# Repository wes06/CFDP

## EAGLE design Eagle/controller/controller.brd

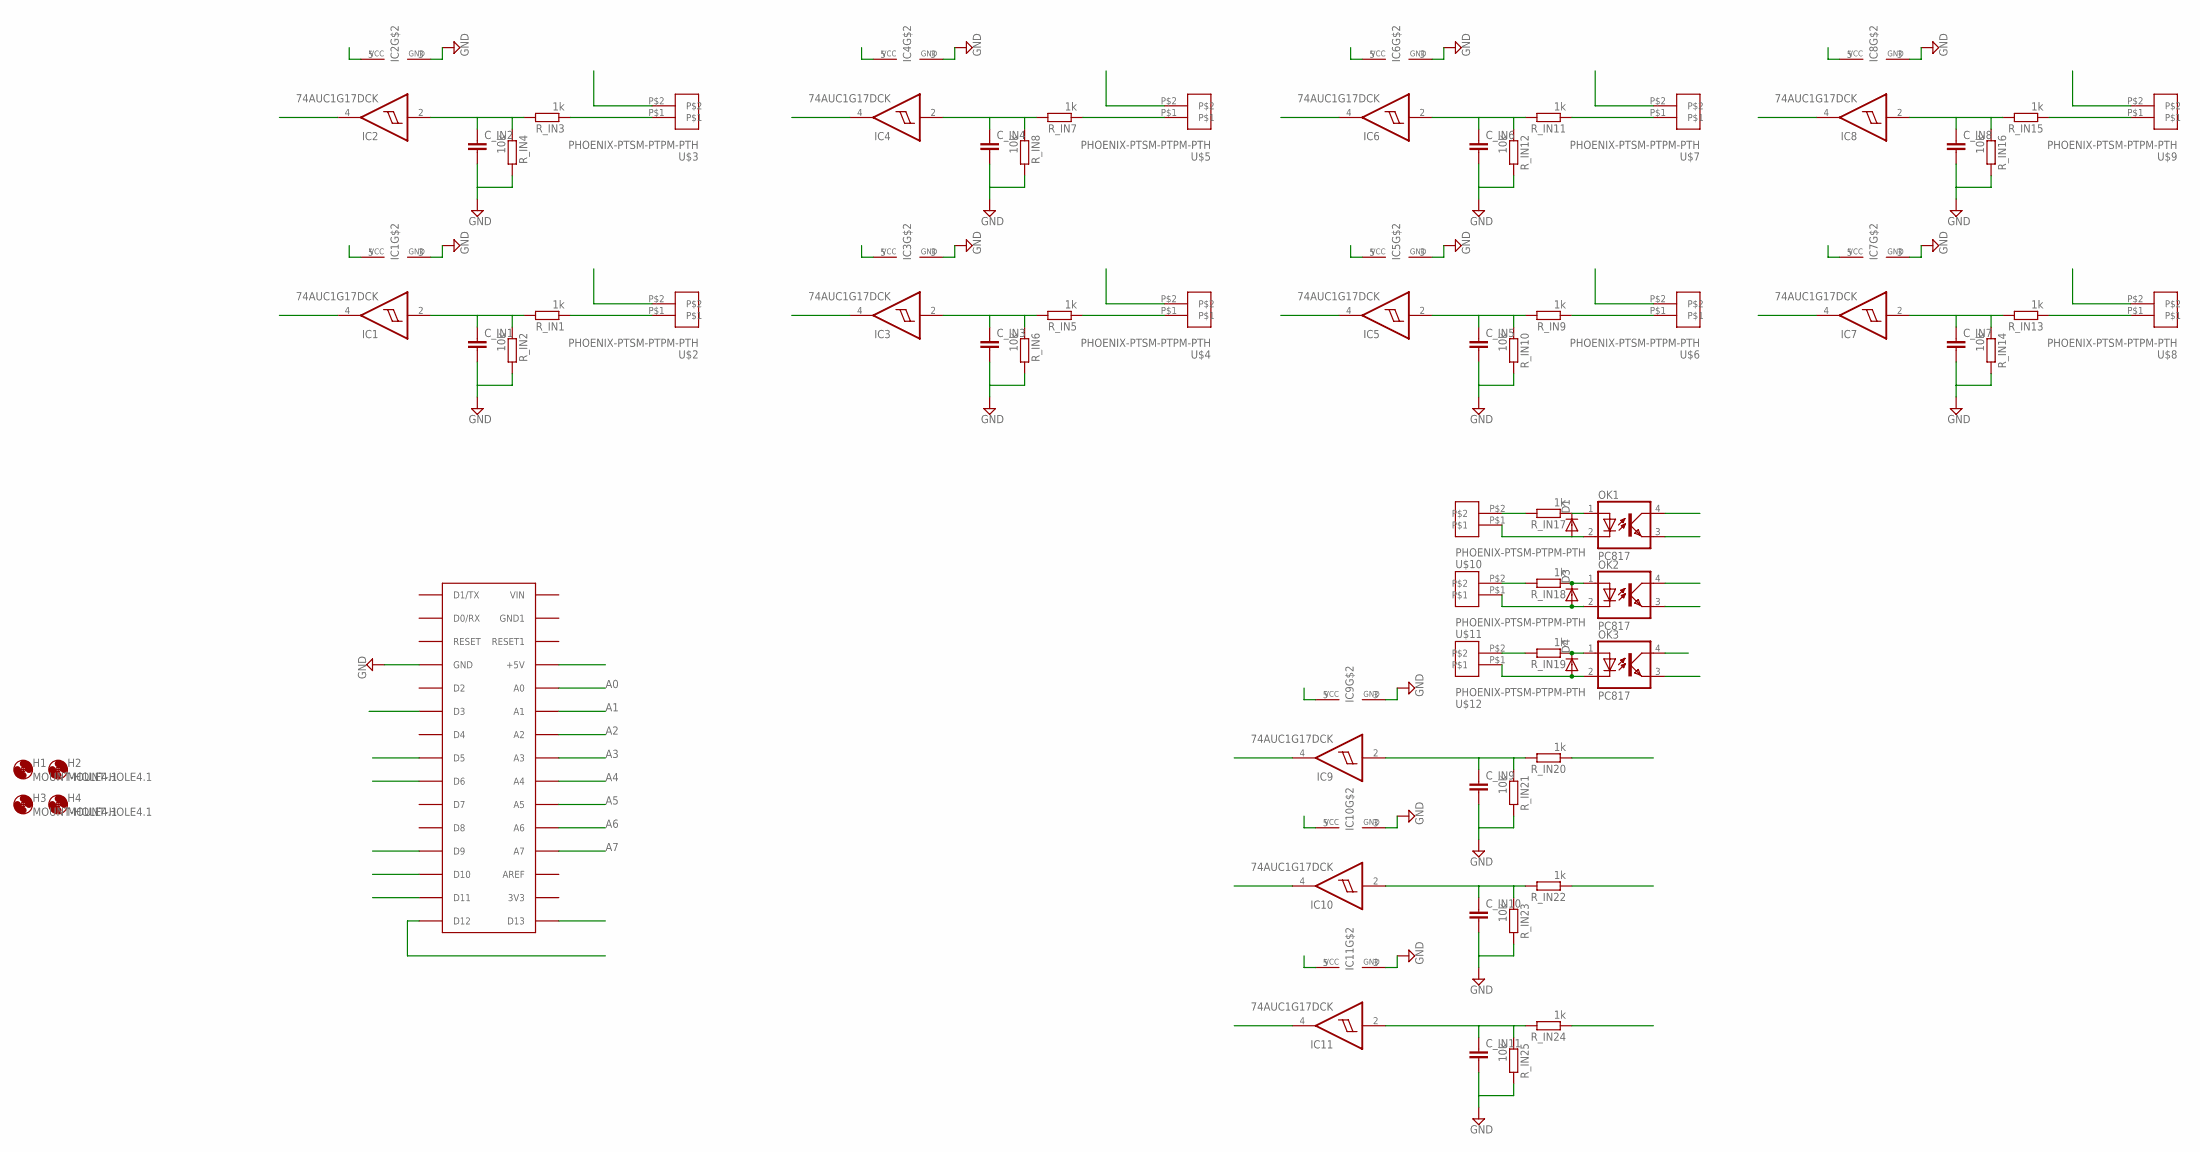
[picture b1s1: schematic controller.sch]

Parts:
C_IN1, C_IN2, C_IN3, C_IN4, C_IN5, C_IN6, C_IN7, C_IN8, C_IN9, C_IN10, C_IN11: C-EUC0805; C0805
D1, D3, D4: DIODE-DO-214AC; DO-214AC
H1, H2, H3, H4: MOUNT-HOLE4.1; 4,1
IC1, IC2, IC3, IC4, IC5, IC6, IC7, IC8, IC9, IC10, IC11: 74AUC1G17DCK; SC70-5
OK1, OK2: PC817; DIL04
OK3: PC817; DIL04; MPN PC817X4J000F
R_IN1, R_IN3, R_IN5, R_IN7, R_IN9, R_IN11, R_IN13, R_IN15, R_IN20, R_IN22, R_IN24: 1k; M0805
R_IN2, R_IN4, R_IN6, R_IN8, R_IN10, R_IN12, R_IN14, R_IN16, R_IN21, R_IN23, R_IN25: 10k; M0805
R_IN17, R_IN18, R_IN19: 1k; M1206
U$1: ARDUINONANO; PDIP-32
U$2, U$3, U$4, U$5, U$6, U$7, U$8, U$9, U$10, U$11, U$12: PHOENIX-PTSM-PTPM-PTH; PTSM-PTH-2.5MM-2

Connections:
+5V: IC1.5 (VCC), IC2.5 (VCC), IC3.5 (VCC), IC4.5 (VCC), IC5.5 (VCC), IC6.5 (VCC), IC7.5 (VCC), IC8.5 (VCC), OK1.4 (COL), OK2.4 (COL), OK3.4 (COL), U$1.+5V, U$2.P$2, U$3.P$2, U$4.P$2, U$5.P$2, U$6.P$2, U$7.P$2, U$8.P$2, U$9.P$2
+5V1: IC9.5 (VCC)
+5V2: IC10.5 (VCC)
+5V3: IC11.5 (VCC)
A0: IC1.4 (O), U$1.A0
A1: IC2.4 (O), U$1.A1
A2: IC3.4 (O), U$1.A2
A3: IC4.4 (O), U$1.A3
A4: IC5.4 (O), U$1.A4
A5: IC6.4 (O), U$1.A5
A6: IC7.4 (O), U$1.A6
A7: IC8.4 (O), U$1.A7
A8: R_IN3.1, U$3.P$1
A9: R_IN5.1, U$4.P$1
A10: R_IN7.1, U$5.P$1
A11: R_IN9.1, U$6.P$1
A12: R_IN11.1, U$7.P$1
A13: R_IN13.1, U$8.P$1
A14: R_IN15.1, U$9.P$1
A15: IC9.4 (O)
A16: IC10.4 (O)
A17: IC11.4 (O)
GND: C_IN1.2, C_IN2.2, C_IN3.2, C_IN4.2, C_IN5.2, C_IN6.2, C_IN7.2, C_IN8.2, C_IN9.2, C_IN10.2, C_IN11.2, IC1.3 (GND), IC2.3 (GND), IC3.3 (GND), IC4.3 (GND), IC5.3 (GND), IC6.3 (GND), IC7.3 (GND), IC8.3 (GND), IC9.3 (GND), IC10.3 (GND), IC11.3 (GND), R_IN2.2, R_IN4.2, R_IN6.2, R_IN8.2, R_IN10.2, R_IN12.2, R_IN14.2, R_IN16.2, R_IN21.2, R_IN23.2, R_IN25.2, U$1.GND
unnamed: C_IN9.1, IC9.2 (I), R_IN20.2, R_IN21.1
unnamed: C_IN2.1, IC2.2 (I), R_IN3.2, R_IN4.1
unnamed: D3.C, OK2.1 (A), R_IN18.1
unnamed: C_IN3.1, IC3.2 (I), R_IN5.2, R_IN6.1
unnamed: D4.C, OK3.1 (A), R_IN19.1
unnamed: C_IN4.1, IC4.2 (I), R_IN7.2, R_IN8.1
unnamed: D1.C, OK1.1 (A), R_IN17.1
unnamed: C_IN5.1, IC5.2 (I), R_IN9.2, R_IN10.1
unnamed: D3.A, OK2.2 (C), U$11.P$1
unnamed: C_IN6.1, IC6.2 (I), R_IN11.2, R_IN12.1
unnamed: D4.A, OK3.2 (C), U$12.P$1
unnamed: C_IN7.1, IC7.2 (I), R_IN13.2, R_IN14.1
unnamed: R_IN17.2, U$10.P$2
unnamed: C_IN8.1, IC8.2 (I), R_IN15.2, R_IN16.1
unnamed: C_IN1.1, IC1.2 (I), R_IN1.2, R_IN2.1
unnamed: R_IN18.2, U$11.P$2
unnamed: R_IN19.2, U$12.P$2
unnamed: D1.A, OK1.2 (C), U$10.P$1
unnamed: C_IN10.1, IC10.2 (I), R_IN22.2, R_IN23.1
unnamed: C_IN11.1, IC11.2 (I), R_IN24.2, R_IN25.1
unnamed: OK1.3 (EMIT), R_IN20.1
unnamed: OK2.3 (EMIT), R_IN22.1
unnamed: OK3.3 (EMIT), R_IN24.1
unnamed: R_IN1.1, U$2.P$1
PWM1: U$1.D3
PWM2: U$1.D5
PWM3: U$1.D6
PWM4: U$1.D9
PWM5: U$1.D10
PWM6: U$1.D11

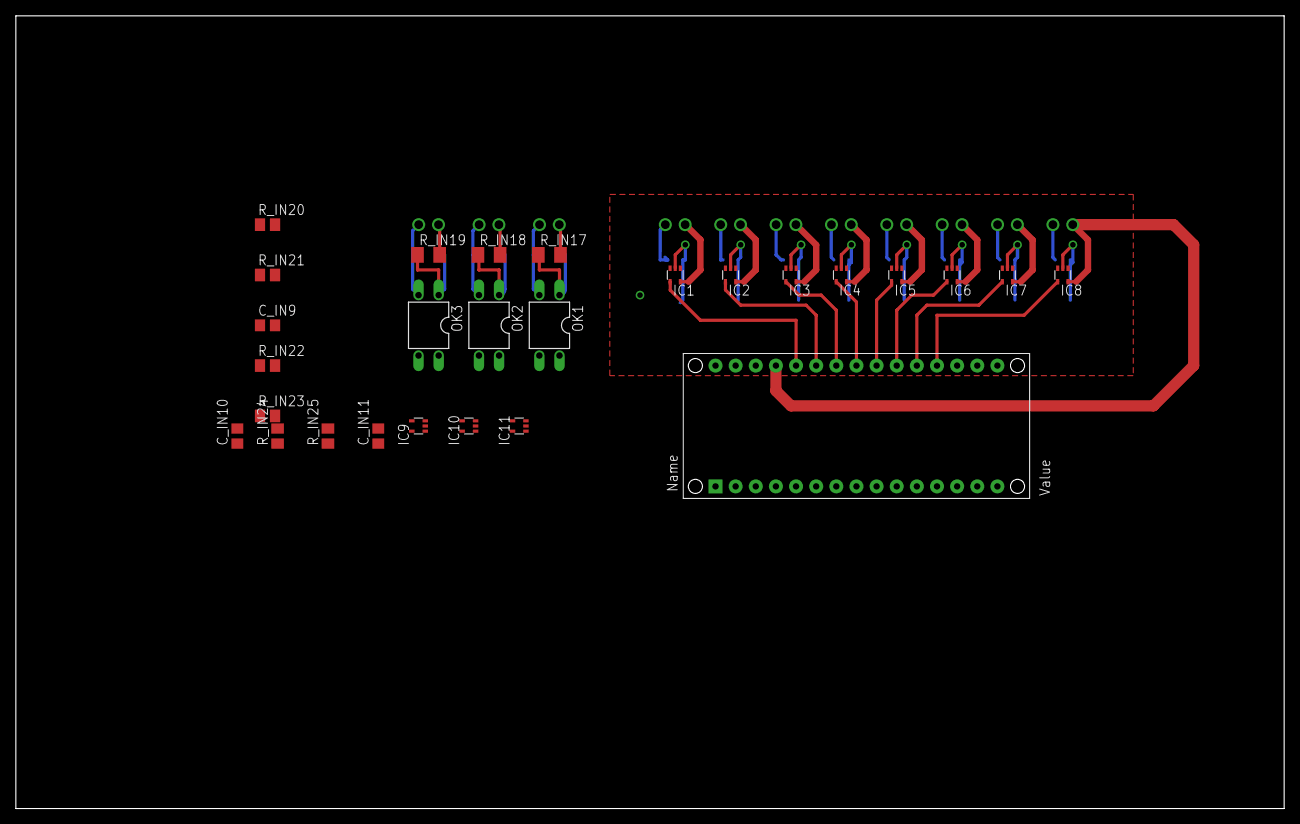
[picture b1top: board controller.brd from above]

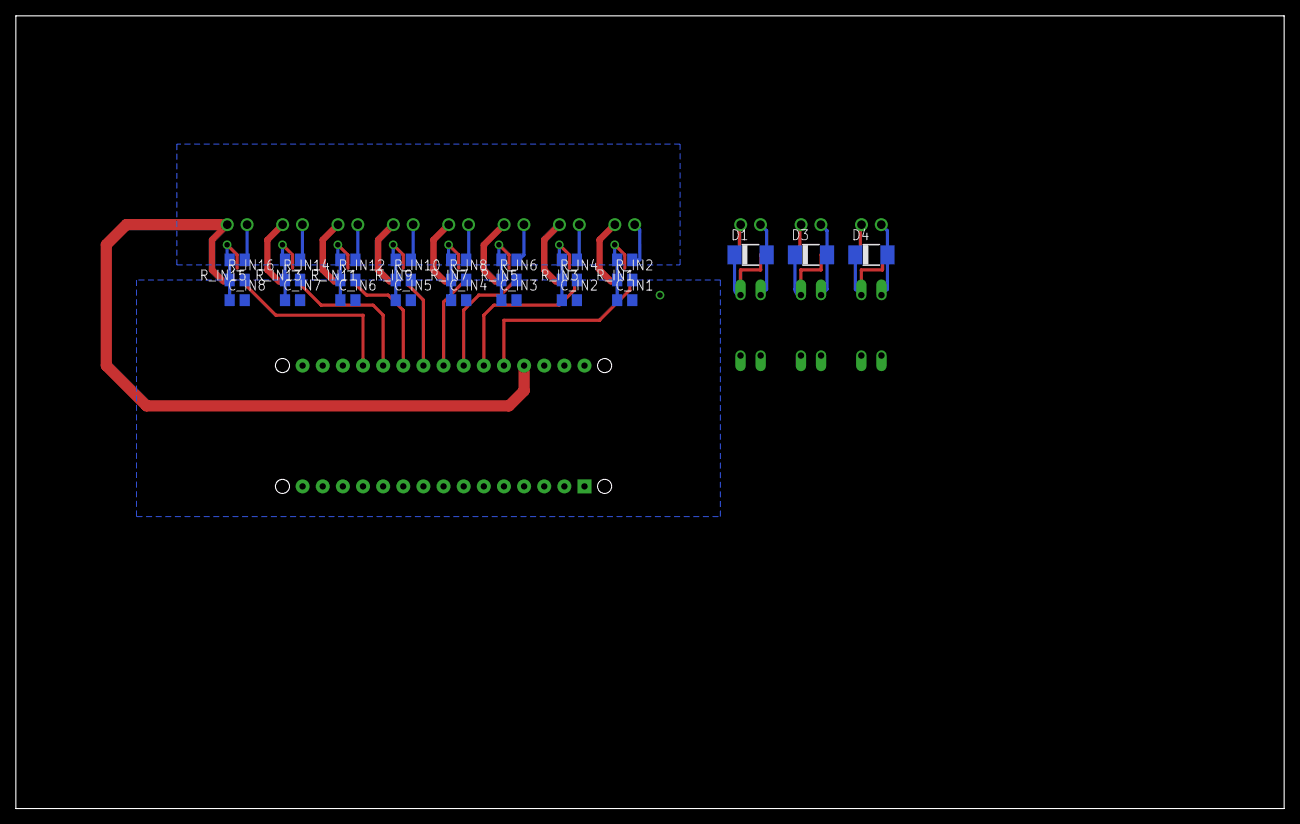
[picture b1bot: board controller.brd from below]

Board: 2 copper layers, 160.0 x 100.0 mm, 69 parts (27 on the bottom side), 41 nets.

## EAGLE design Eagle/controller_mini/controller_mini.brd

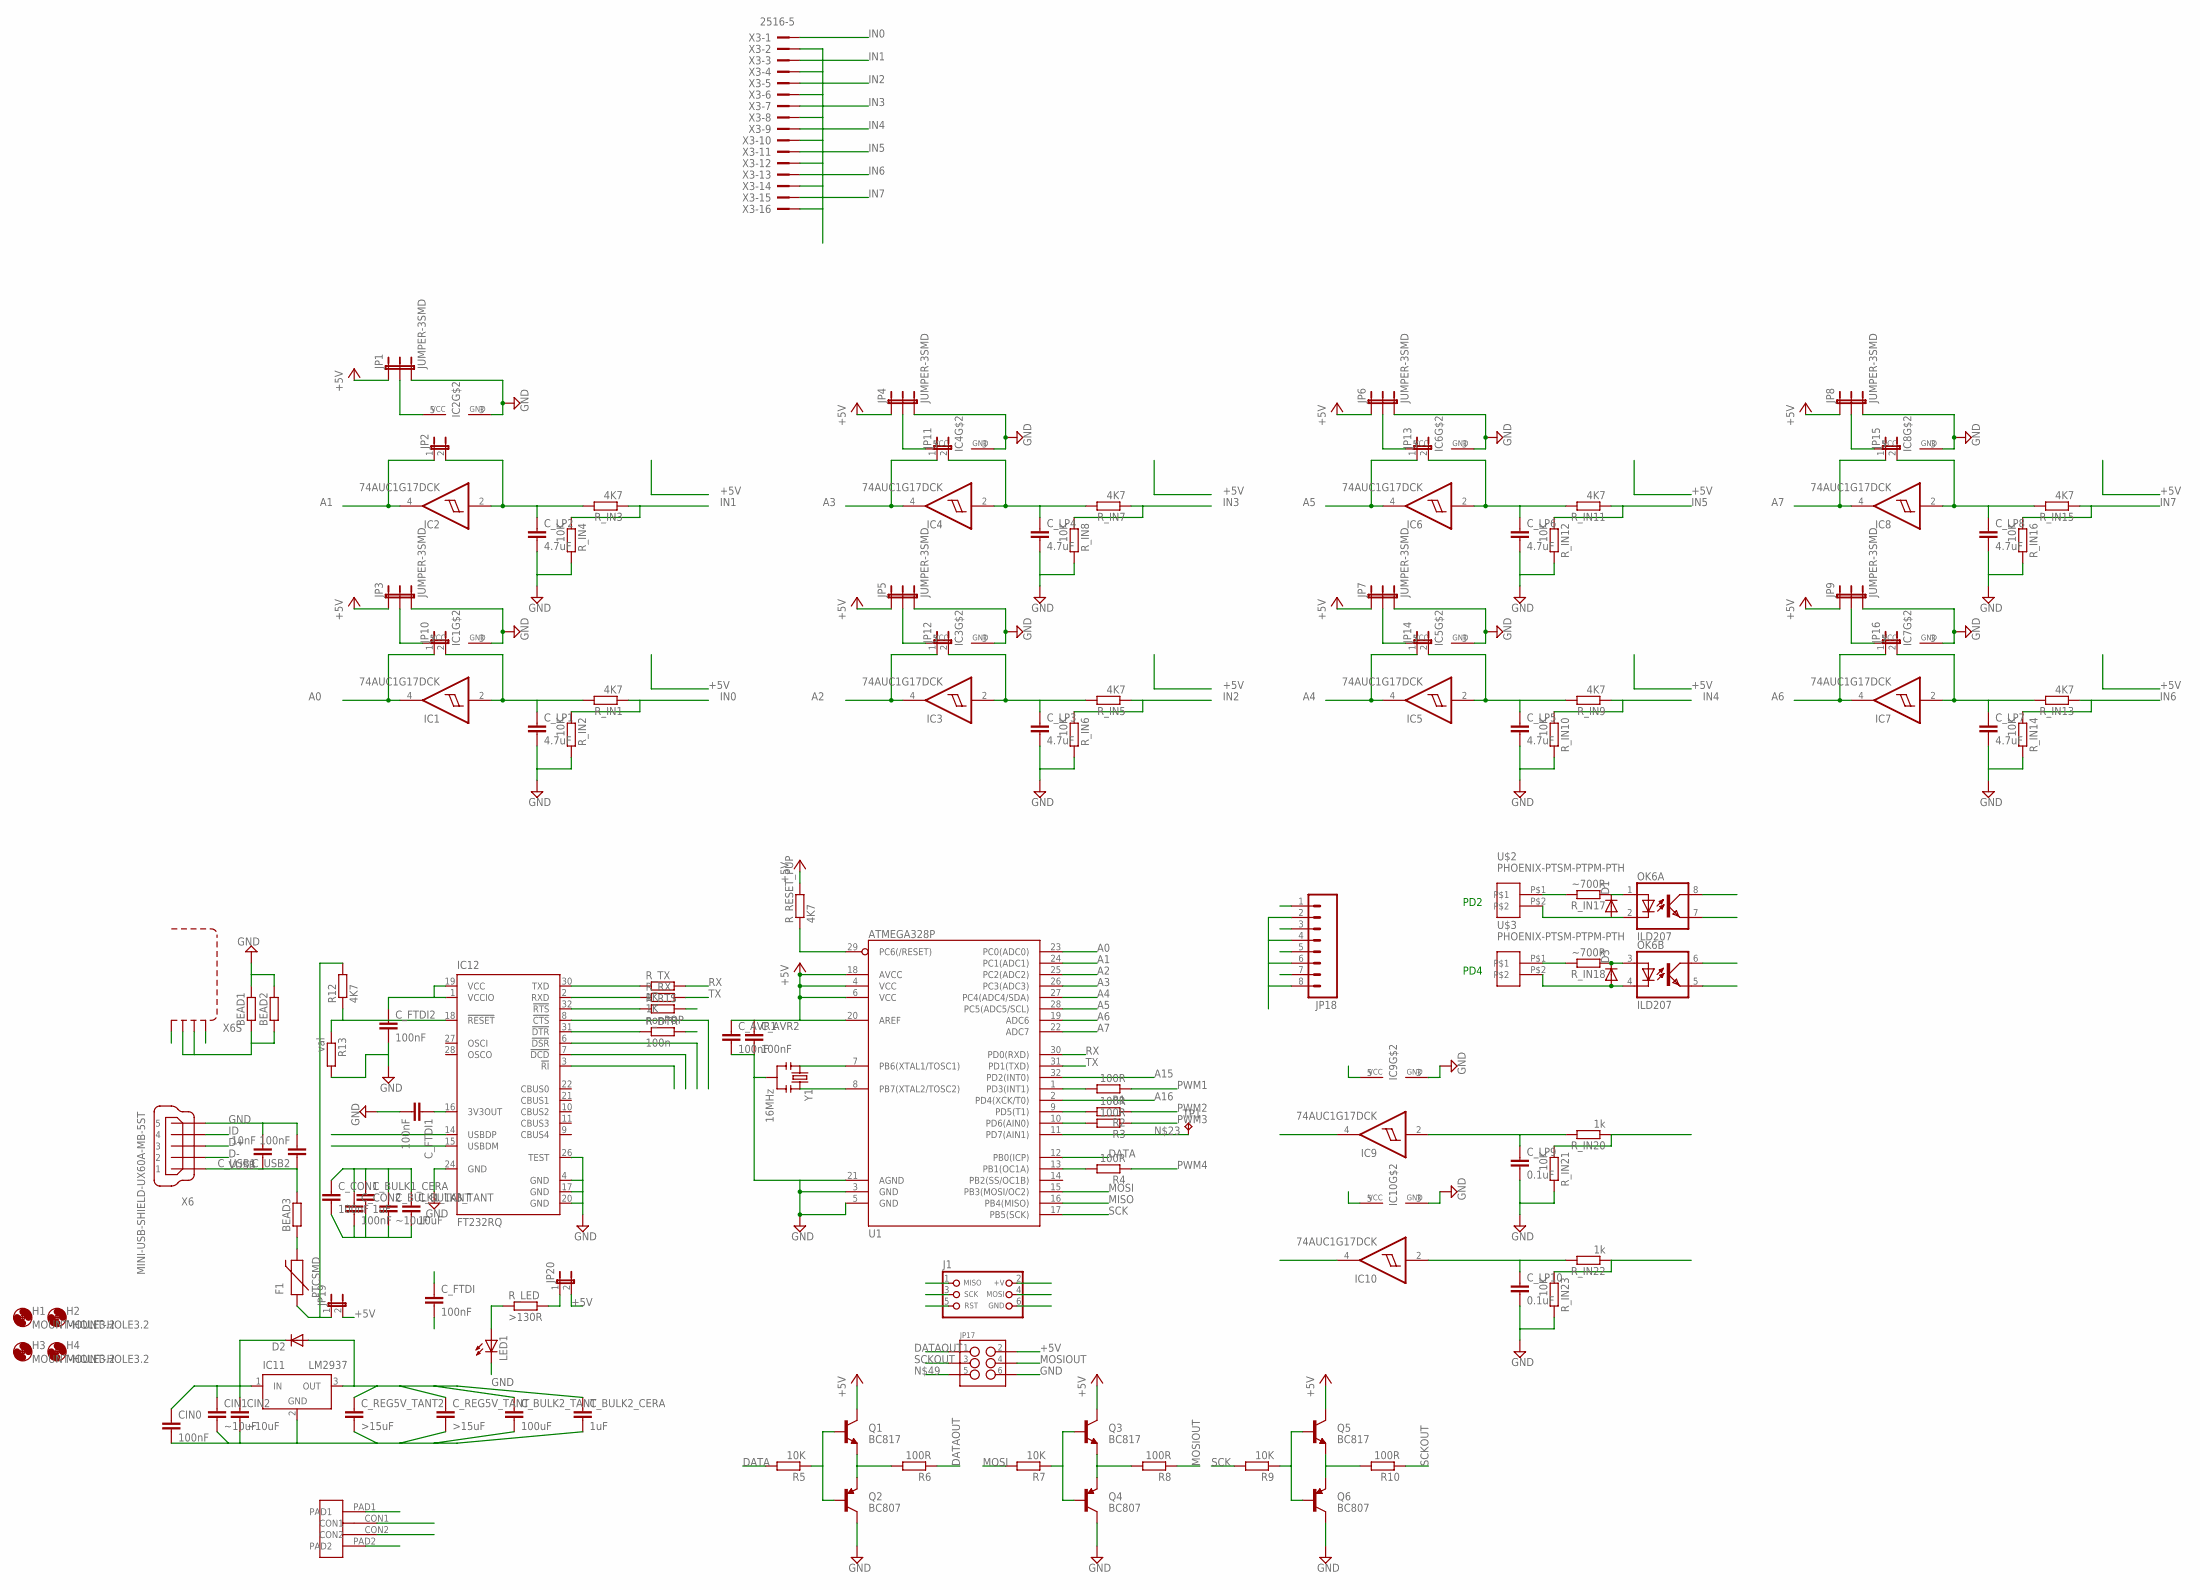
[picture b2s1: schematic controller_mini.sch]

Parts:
BEAD1, BEAD2, BEAD3: R-EU_R0805; R0805
CIN0: 100nF; C0805
CIN1, CIN2: ~10uF; C1210
C_AVR1, C_AVR2: 100nF; C0805
C_BULK1_CERA, C_BULK2_CERA: 1uF; C0805K
C_BULK1_TANT: ~10uF; C1210
C_BULK2_TANT: 100uF; C1210
C_BULK3_TANT: 10uF; C1210
C_CON1, C_CON2: 100nF; C0805
C_FTDI, C_FTDI1, C_FTDI2: 100nF; C0805
C_LP1, C_LP2, C_LP3, C_LP4, C_LP5, C_LP6, C_LP7, C_LP8: 4.7uF; C0805
C_LP9, C_LP10: 0.1uF; C0805
C_REG5V_TANT, C_REG5V_TANT2: >15uF; C1210
C_USB1: 10nF; C0805
C_USB2: 100nF; C0805
D1, D3: DIODE-MICROMELF-W; MICROMELF-W
D2: DIODESMA; SMA-DIODE
F1: PTCSMD; PTC-1206
H1, H2, H3, H4: MOUNT-HOLE3.2; 3,2
IC1, IC2, IC3, IC4, IC5, IC6, IC7, IC8, IC9, IC10: 74AUC1G17DCK; SC70-5
IC11: LM2937; SOT223
IC12: FT232RQ; QFN32
J1: CON_HEADER_PRG_AVR_ICSP; HEADER_PRG_2X03
JP1, JP3, JP4, JP5, JP6, JP7, JP8, JP9: JUMPER-3SMD; SJ_3
JP2, JP10, JP11, JP12, JP13, JP14, JP15, JP16: JUMPER-2SMD-NO; SJ_2S-NO
JP17: M03X2NO_SILK; 2X3-NS
JP18: M08LOCK; 1X08_LOCK
JP19, JP20: JUMPER-2SMD-NC; SJ_2S
LED1: LEDCHIP-LED0805; CHIP-LED0805
OK6: ILD207; SOIC08
Q1, Q3, Q5: BC817; SOT23-3
Q2, Q4, Q6: BC807; SOT23-3
R1, R2, R3, R6, R8, R10: 100R; M0805
R4: 100R; R0805W
R5, R7, R9: 10K; M0805
R12: 4K7; R0805
R13: val; R0805
R_DTR: 100n; M0805
R_IN1, R_IN3, R_IN5, R_IN7, R_IN9, R_IN11, R_IN13, R_IN15: 4K7; M0805
R_IN2, R_IN4, R_IN6, R_IN8, R_IN10, R_IN12, R_IN14, R_IN16, R_IN21, R_IN23: 10K; M0805
R_IN17, R_IN18: ~700R; M1206
R_IN20, R_IN22: 1k; M0805
R_LED: >130R; M0805
R_RESET_PUP: 4K7; M0805
R_RTS: nonPOP; M0805
R_RX: 1K; M0805
R_TX: 1K; M0805
TP1: TPTP10R; TP10R
U1: ATMEGA328P; TQFP32-08
U$1: PHOENIX-PTSM-PTPM; PTSM-SMD-2.5MM-2
U$2, U$3: PHOENIX-PTSM-PTPM-PTH; PTSM-PTH-2.5MM-2
X3: 2516-5; PAK100/2500-5-16
X6: MINI-USB-SHIELD-UX60A-MB-5ST; UX60A-MB-5ST
Y1: 16MHz; RESONATOR-SMD

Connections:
+5V: C_AVR1.1, C_AVR2.1, C_BULK1_CERA.1, C_BULK1_TANT.1, C_BULK2_CERA.1, C_BULK2_TANT.1, C_BULK3_TANT.1, C_CON1.1, C_CON2.1, C_FTDI.1, C_FTDI2.1, C_REG5V_TANT.1, C_REG5V_TANT2.1, D2.A, IC9.5 (VCC), IC10.5 (VCC), IC11.3 (OUT), IC12.1 (VCCIO), IC12.19 (VCC), J1.2 (+V), JP1.1, JP3.1, JP4.1, JP5.1, JP6.1, JP7.1, JP8.1, JP9.1, JP17.2, JP19.2, JP20.2, OK6.6 (COL), OK6.8 (COL), Q1.3 (C), Q3.3 (C), Q5.3 (C), R_RESET_PUP.2, U1.4 (VCC), U1.6 (VCC), U1.18 (AVCC), U1.20 (AREF), X3.2, X3.4, X3.6, X3.8, X3.10, X3.12, X3.14, X3.16
A0: IC1.4 (O), JP10.1, U1.23 (PC0(ADC0))
A1: IC2.4 (O), JP2.1, U1.24 (PC1(ADC1))
A2: IC3.4 (O), JP12.1, U1.25 (PC2(ADC2))
A3: IC4.4 (O), JP11.1, U1.26 (PC3(ADC3))
A4: IC5.4 (O), JP14.1, U1.27 (PC4(ADC4/SDA))
A5: IC6.4 (O), JP13.1, U1.28 (PC5(ADC5/SCL))
A6: IC7.4 (O), JP16.1, U1.19 (ADC6)
A7: IC8.4 (O), JP15.1, U1.22 (ADC7)
A15: IC9.4 (O), U1.32 (PD2(INT0))
A16: IC10.4 (O), U1.2 (PD4(XCK/T0))
D+: IC12.14 (USBDP), X6.3
D-: IC12.15 (USBDM), X6.2
DATA: R5.2, U1.12 (PB0(ICP))
DATAOUT: JP17.1, R6.1
EROUTE: C_LP8.1, IC8.2 (I), JP15.2, R_IN15.2
GND: BEAD1.2, BEAD2.2, CIN0.2, CIN1.2, CIN2.2, C_AVR1.2, C_AVR2.2, C_BULK1_CERA.2, C_BULK1_TANT.2, C_BULK2_CERA.2, C_BULK2_TANT.2, C_BULK3_TANT.2, C_CON1.2, C_CON2.2, C_FTDI.2, C_FTDI1.2, C_FTDI2.2, C_LP1.2, C_LP2.2, C_LP3.2, C_LP4.2, C_LP5.2, C_LP6.2, C_LP7.2, C_LP8.2, C_LP9.2, C_LP10.2, C_REG5V_TANT.2, C_REG5V_TANT2.2, C_USB1.2, C_USB2.2, IC1.3 (GND), IC2.3 (GND), IC3.3 (GND), IC4.3 (GND), IC5.3 (GND), IC6.3 (GND), IC7.3 (GND), IC8.3 (GND), IC9.3 (GND), IC10.3 (GND), IC11.2 (GND), IC11.4 (GND), IC12.4 (GND), IC12.17 (GND), IC12.20 (GND), IC12.24 (GND), IC12.26 (TEST), J1.6 (GND), JP1.3, JP3.3, JP4.3, JP5.3, JP6.3, JP7.3, JP8.3, JP9.3, JP17.6, JP18.2, JP18.4, JP18.6, JP18.8, LED1.C, Q2.3 (C), Q4.3 (C), Q6.3 (C), R13.2, R_IN2.2, R_IN4.2, R_IN6.2, R_IN8.2, R_IN10.2, R_IN12.2, R_IN14.2, R_IN16.2, R_IN21.2, R_IN23.2, U1.3 (GND), U1.5 (GND), U1.21 (AGND), U$1.CON2, U$1.PAD1, U$1.PAD2, X6.5, Y1.2
ID: X6.4
IN0: R_IN1.1, R_IN2.1, X3.1
IN1: R_IN3.1, R_IN4.1, X3.3
IN2: R_IN5.1, R_IN6.1, X3.5
IN3: R_IN7.1, R_IN8.1, X3.7
IN4: R_IN9.1, R_IN10.1, X3.9
IN5: R_IN11.1, R_IN12.1, X3.11
IN6: R_IN13.1, R_IN14.1, X3.13
IN7: R_IN15.1, R_IN16.1, X3.15
INFOMOVE: D3.A, OK6.4 (C), U$3.P$2
MISO: J1.1 (MISO), U1.16 (PB4(MISO))
MOSI: J1.4 (MOSI), R7.2, U1.15 (PB3(MOSI/OC2))
MOSIOUT: JP17.4, R8.1
unnamed: C_LP9.1, IC9.2 (I), R_IN20.2
unnamed: C_LP2.1, IC2.2 (I), JP2.2, R_IN3.2
unnamed: D3.C, OK6.3 (A), R_IN18.1
unnamed: C_LP3.1, IC3.2 (I), JP12.2, R_IN5.2
unnamed: U1.7 (PB6(XTAL1/TOSC1)), Y1.1
unnamed: C_LP4.1, IC4.2 (I), JP11.2, R_IN7.2
unnamed: D1.C, OK6.1 (A), R_IN17.1
unnamed: C_LP5.1, IC5.2 (I), JP14.2, R_IN9.2
unnamed: BEAD3.1, F1.2
unnamed: C_LP6.1, IC6.2 (I), JP13.2, R_IN11.2
unnamed: U1.8 (PB7(XTAL2/TOSC2)), Y1.3
unnamed: C_LP7.1, IC7.2 (I), JP16.2, R_IN13.2
unnamed: R_IN17.2, U$2.P$1
unnamed: JP20.1, R_LED.2
unnamed: C_LP1.1, IC1.2 (I), JP10.2, R_IN1.2
unnamed: R_IN18.2, U$3.P$1
unnamed: Q1.2 (E), Q2.2 (E), R6.2
unnamed: D1.A, OK6.2 (C), U$2.P$2
unnamed: C_LP10.1, IC10.2 (I), R_IN22.2
unnamed: Q1.1 (B), Q2.1 (B), R5.1
unnamed: OK6.7 (EMIT), R_IN20.1, R_IN21.1
unnamed: OK6.5 (EMIT), R_IN22.1, R_IN23.1
unnamed: TP1.TP, U1.11 (PD7(AIN1))
unnamed: IC12.30 (TXD), R_TX.1
unnamed: IC12.2 (RXD), R_RX.1
unnamed: IC12.32 (!RTS), R_RTS.1
unnamed: IC12.31 (!DTR), R_DTR.1
unnamed: C_FTDI1.1, IC12.16 (3V3OUT)
unnamed: IC2.5 (VCC), JP1.2
unnamed: IC1.5 (VCC), JP3.2
unnamed: IC4.5 (VCC), JP4.2
unnamed: IC3.5 (VCC), JP5.2
unnamed: IC6.5 (VCC), JP6.2
unnamed: IC5.5 (VCC), JP7.2
unnamed: IC8.5 (VCC), JP8.2
unnamed: IC7.5 (VCC), JP9.2
unnamed: IC12.18 (!RESET), R12.1, R13.1
unnamed: Q3.2 (E), Q4.2 (E), R8.2
unnamed: Q3.1 (B), Q4.1 (B), R7.1
unnamed: R1.2, U1.1 (PD3(INT1))
unnamed: R2.2, U1.9 (PD5(T1))
unnamed: R3.2, U1.10 (PD6(AIN0))
unnamed: R4.2, U1.13 (PB1(OC1A))
unnamed: LED1.A, R_LED.1
unnamed: Q5.2 (E), Q6.2 (E), R10.2
unnamed: Q5.1 (B), Q6.1 (B), R9.1
unnamed: BEAD1.1, BEAD2.1, X6.M2 (S2), X6.M3 (S3)
unnamed: F1.1, JP19.1, R12.2
PWM1: JP18.1, R1.1
PWM2: JP18.3, R2.1
PWM3: JP18.5, R3.1
PWM4: JP18.7, R4.1
RESET: J1.5 (RST), R_DTR.2, R_RESET_PUP.1, R_RTS.2, U1.29 (PC6(/RESET))
RX: R_TX.2, U1.30 (PD0(RXD))
SCK: J1.3 (SCK), R9.2, U1.17 (PB5(SCK))
SCKOUT: JP17.3, R10.1
TX: R_RX.2, U1.31 (PD1(TXD))
VIN: CIN0.1, CIN1.1, CIN2.1, D2.C, IC11.1 (IN), U$1.CON1
VUSB: BEAD3.2, C_USB1.1, C_USB2.1, X6.1

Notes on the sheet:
PD4
PD2

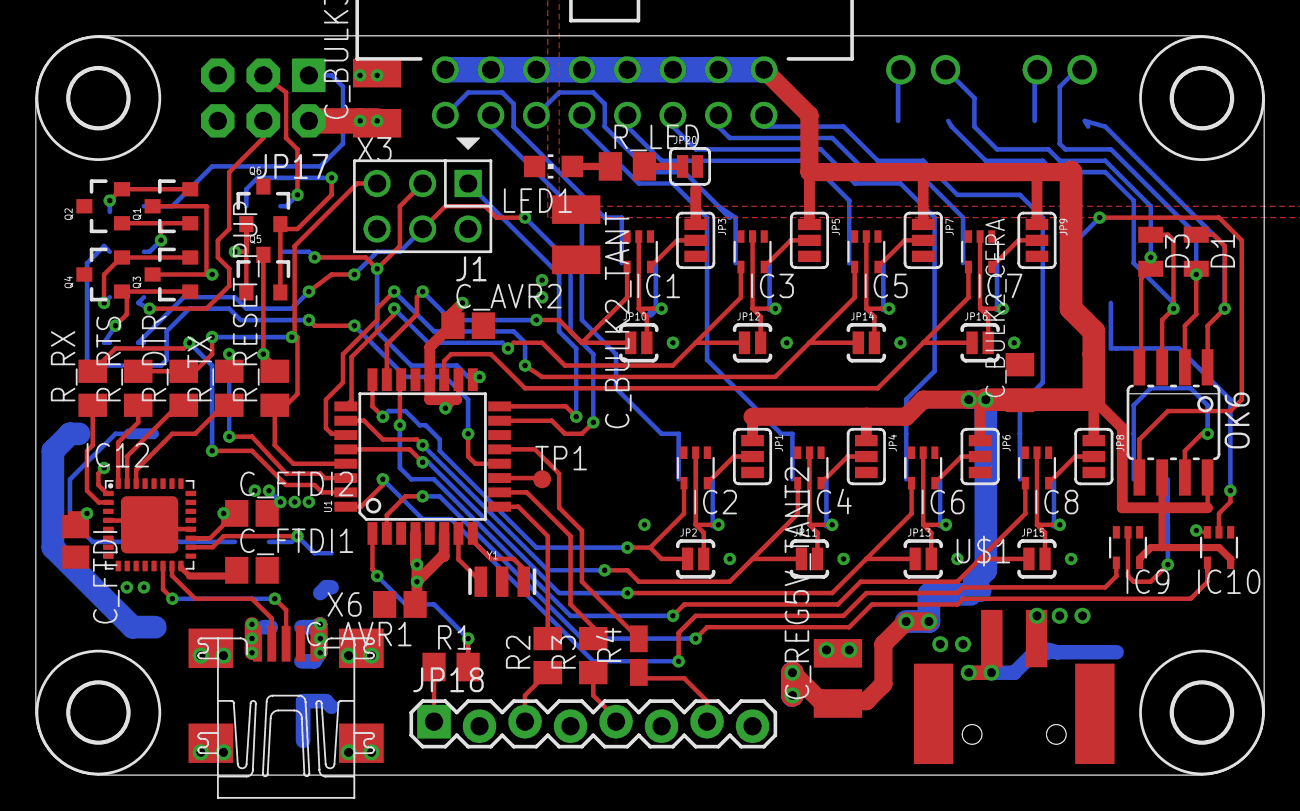
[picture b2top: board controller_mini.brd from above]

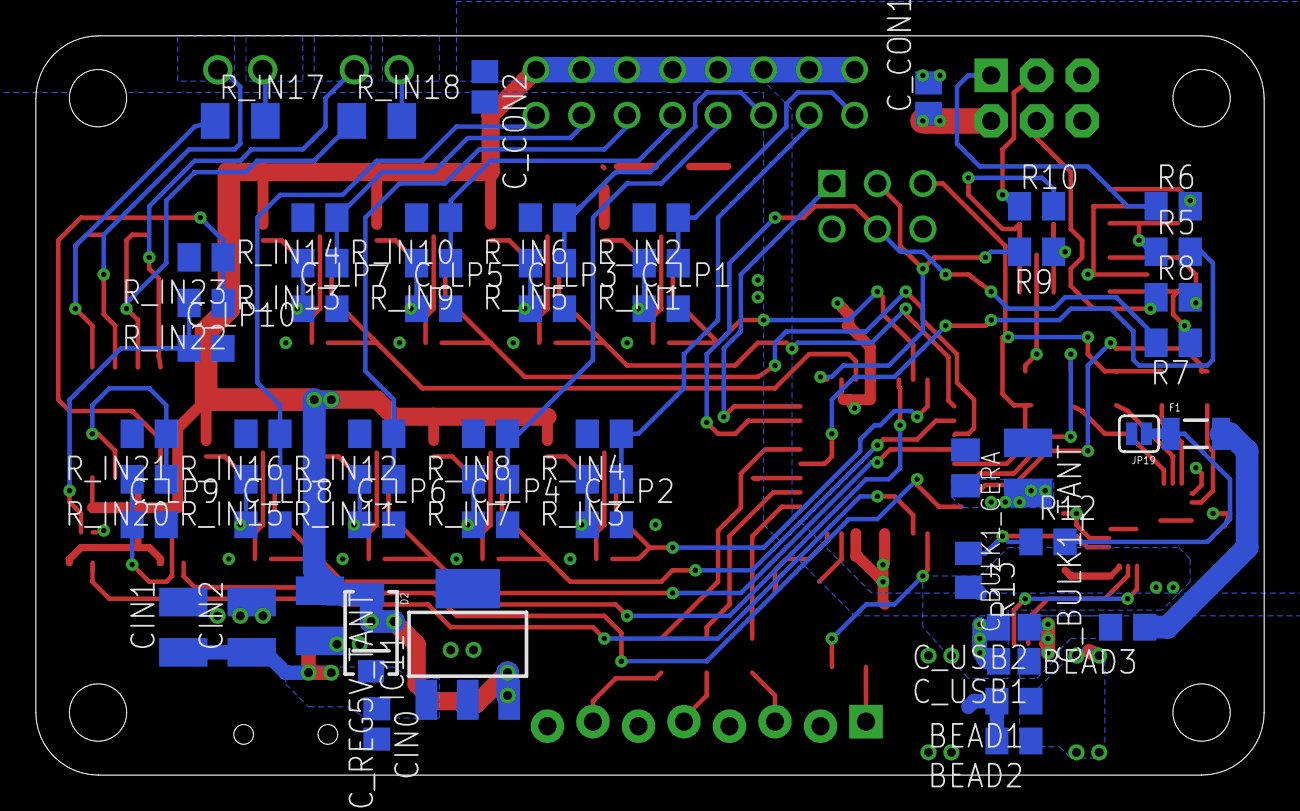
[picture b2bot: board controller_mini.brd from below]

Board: 2 copper layers, 68.6 x 41.3 mm, 129 parts (57 on the bottom side), 88 nets.

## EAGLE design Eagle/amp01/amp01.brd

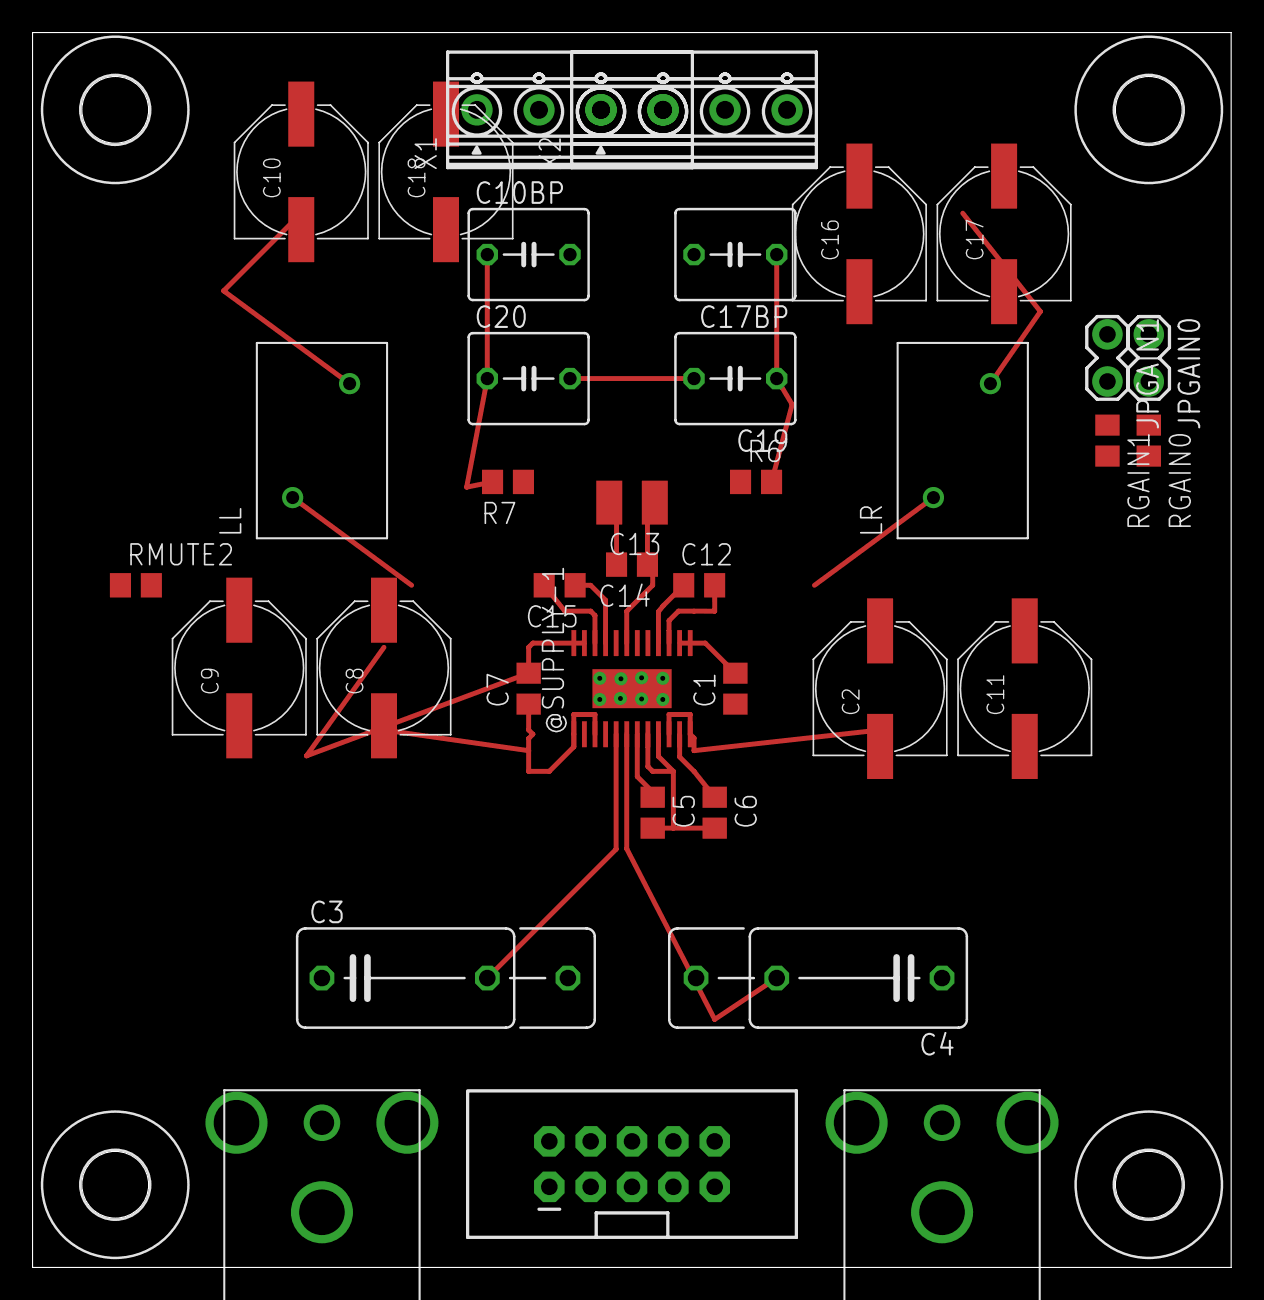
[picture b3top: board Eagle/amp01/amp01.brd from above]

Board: 2 copper layers, 73.6 x 75.9 mm, 41 parts (0 on the bottom side), 21 nets.

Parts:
@SUPPLY-1: TPA3123; PWP-TSSOP24
C1, C7, C14: .1uF; C0805
C2, C8, C9, C10, C11, C16, C17, C18: 220uF; PANASONIC_F
C3, C4: 1uF; C102_152-062X184
C5, C6: 1uF; C0805
C10BP, C17BP, C19, C20: 0.68uF; C050-055X075
C12, C15: .22uF; C0805
C13: 10uF; C1210
H1, H2, H3, H4: MOUNT-HOLE4.1; 4,1
JP3: M05X2SHD_LOCK; 2X5-SHROUDED_LOCK
JPGAIN0, JPGAIN1: 1X02_LOCK
LIN: RCA-NYS354; NYS354
LL: 1D10A; 1D10APAC
LR: 1D10A; 1D10APAC
R6, R7: 4K7; R0805
RGAIN0, RGAIN1: 10K; R0805
RIN: RCA-NYS354; NYS354
RMUTE2: 10K; R0805
X1, X2: 1727036

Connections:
GND: @SUPPLY-1.8, @SUPPLY-1.9, @SUPPLY-1.13, @SUPPLY-1.14, @SUPPLY-1.23, @SUPPLY-1.24, C1.2, C5.2, C6.2, C7.2, C13.2, C14.2, C19.2, C20.2, JP3.9, JP3.10, JPGAIN0.1, JPGAIN1.1, LIN.P$2, LIN.P$3, LIN.P$4, R6.1, R7.1, RIN.P$2, RIN.P$3, RIN.P$4, RMUTE2.1, X1.1, X1.3, X2.1, X2.3
LIN: JP3.2, LIN.SIG
unnamed: @SUPPLY-1.6, C4.2
unnamed: @SUPPLY-1.5, C3.2
unnamed: C3.1, JP3.6
unnamed: C4.1, JP3.5
unnamed: @SUPPLY-1.11, C6.1
unnamed: @SUPPLY-1.4, RMUTE2.2
unnamed: @SUPPLY-1.18, JPGAIN0.2, RGAIN0.2
unnamed: @SUPPLY-1.17, JPGAIN1.2, RGAIN1.2
unnamed: @SUPPLY-1.7, C5.1
unnamed: @SUPPLY-1.15, C12.2, LR.P$1
unnamed: @SUPPLY-1.16, C12.1
unnamed: @SUPPLY-1.22, C15.2, LL.P$1
unnamed: @SUPPLY-1.21, C15.1
unnamed: C10BP.1, C18.+, C20.1, LL.P$2, R7.2
unnamed: C16.-, C17BP.2, X1.4
unnamed: C10BP.2, C18.-, X1.2
unnamed: C16.+, C17BP.1, C19.1, LR.P$2, R6.2
RIN: JP3.1, RIN.SIG
VCC: @SUPPLY-1.1, @SUPPLY-1.3, @SUPPLY-1.10, @SUPPLY-1.12, @SUPPLY-1.19, @SUPPLY-1.20, C1.1, C7.1, C13.1, C14.1, RGAIN0.1, RGAIN1.1, X2.2, X2.4

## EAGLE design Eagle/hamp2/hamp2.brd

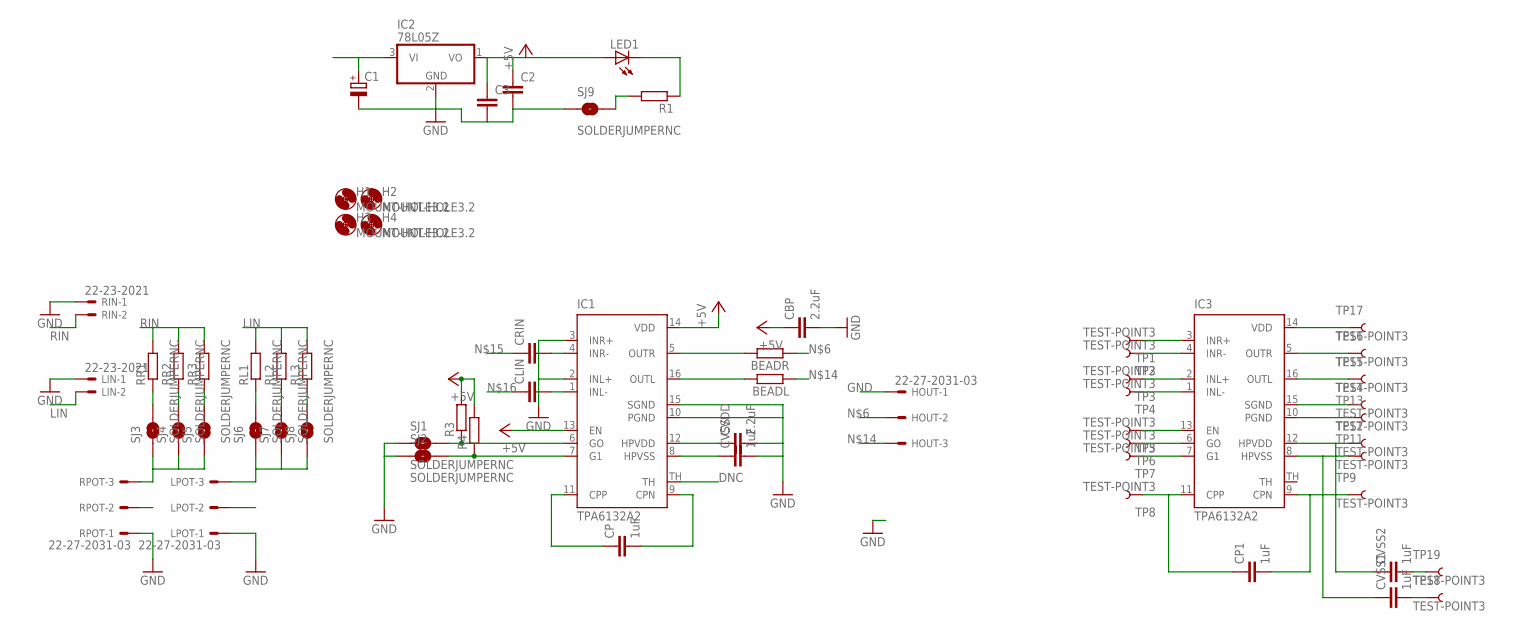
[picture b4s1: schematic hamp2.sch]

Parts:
BEADL: R-EU_R0805; R0805
BEADR: R-EU_R0805; R0805
C1: CPOL-EUF; PANASONIC_F
C2: C-EUC1210; C1210
C3: C-EUC0805; C0805
CBP: 2.2uF; C0805
CLIN: C-EU050-055X075; C050-055X075
CP, CP1: 1uF; C0805
CRIN: C-EU050-055X075; C050-055X075
CVDD: 2.2uF; C0805
CVSS, CVSS1, CVSS2: 1uF; C0805
H1, H2, H3, H4: MOUNT-HOLE3.2; 3,2
HOUT: 22-27-2031-03; 6410-03
IC1: TPA6132A2; QFN16
IC2: 78L05Z; TO92
IC3: TPA6132A2; QFN16; MPN TPA6132A2RTET
LED1: LEDCHIP-LED0805; CHIP-LED0805
LIN: 22-23-2021
LPOT: 22-27-2031-03; 6410-03
R1, R3, R4: R-EU_R0805; R0805
RIN: 22-23-2021
RL1, RL2, RL3: R-EU_R0805; R0805
RPOT: 22-27-2031-03; 6410-03
RR1, RR2, RR3: R-EU_R0805; R0805
SJ1, SJ2, SJ3, SJ4, SJ5, SJ6, SJ7, SJ8, SJ9: SOLDERJUMPERNC; SJ_2S
TP1, TP2, TP3, TP4, TP5, TP6, TP7, TP8, TP9, TP11, TP12, TP13, TP14, TP15, TP16, TP17, TP18, TP19: TEST-POINT3; PAD.03X.03

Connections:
+5V: C2.1, C3.1, CBP.1, IC1.13 (EN), IC1.14 (VDD), IC2.1 (VO), LED1.A, R3.2, R4.2
DNC: IC1.TH
GND: C1.-, C2.2, C3.2, CBP.2, CVDD.2, CVSS.2, HOUT.1, IC1.2 (INL+), IC1.3 (INR+), IC1.10 (PGND), IC1.15 (SGND), IC2.2 (GND), LIN.1, LPOT.1, RIN.1, RPOT.1, SJ1.1, SJ2.1, SJ9.1
LIN: LIN.2, RL1.2, RL2.2, RL3.2
unnamed: CVDD.1, IC1.12 (HPVDD)
unnamed: CRIN.2, IC1.4 (INR-)
unnamed: CLIN.2, IC1.1 (INL-)
unnamed: IC1.6 (GO), R3.1, SJ1.2
unnamed: IC1.7 (G1), R4.1, SJ2.2
unnamed: BEADR.1, HOUT.2
unnamed: CP.1, IC1.11 (CPP)
unnamed: CP.2, IC1.9 (CPN)
unnamed: CVSS.1, IC1.8 (HPVSS)
unnamed: BEADR.2, IC1.5 (OUTR)
unnamed: BEADL.2, IC1.16 (OUTL)
unnamed: RR1.1, SJ3.2
unnamed: RR2.1, SJ4.2
unnamed: BEADL.1, HOUT.3
unnamed: CRIN.1, RPOT.2, RR3.1, SJ5.2
unnamed: CLIN.1, LPOT.2, RL3.1, SJ8.2
unnamed: C1.+, IC2.3 (VI)
unnamed: RL1.1, SJ6.2
unnamed: RL2.1, SJ7.2
unnamed: RPOT.3, SJ3.1, SJ4.1, SJ5.1
unnamed: LPOT.3, SJ6.1, SJ7.1, SJ8.1
unnamed: IC3.3 (INR+), TP1.P$1
unnamed: IC3.4 (INR-), TP2.P$1
unnamed: IC3.2 (INL+), TP3.P$1
unnamed: IC3.1 (INL-), TP4.P$1
unnamed: IC3.13 (EN), TP5.P$1
unnamed: IC3.6 (GO), TP6.P$1
unnamed: IC3.7 (G1), TP7.P$1
unnamed: CP1.1, IC3.11 (CPP), TP8.P$1
unnamed: CP1.2, IC3.9 (CPN), TP9.P$1
unnamed: LED1.C, R1.1
unnamed: CVSS1.1, IC3.8 (HPVSS), TP11.P$1
unnamed: CVSS2.1, IC3.12 (HPVDD), TP12.P$1
unnamed: IC3.10 (PGND), TP13.P$1
unnamed: IC3.15 (SGND), TP14.P$1
unnamed: IC3.16 (OUTL), TP15.P$1
unnamed: IC3.5 (OUTR), TP16.P$1
unnamed: IC3.14 (VDD), TP17.P$1
unnamed: CVSS2.2, TP19.P$1
unnamed: CVSS1.2, TP18.P$1
unnamed: R1.2, SJ9.2
RIN: RIN.2, RR1.2, RR2.2, RR3.2

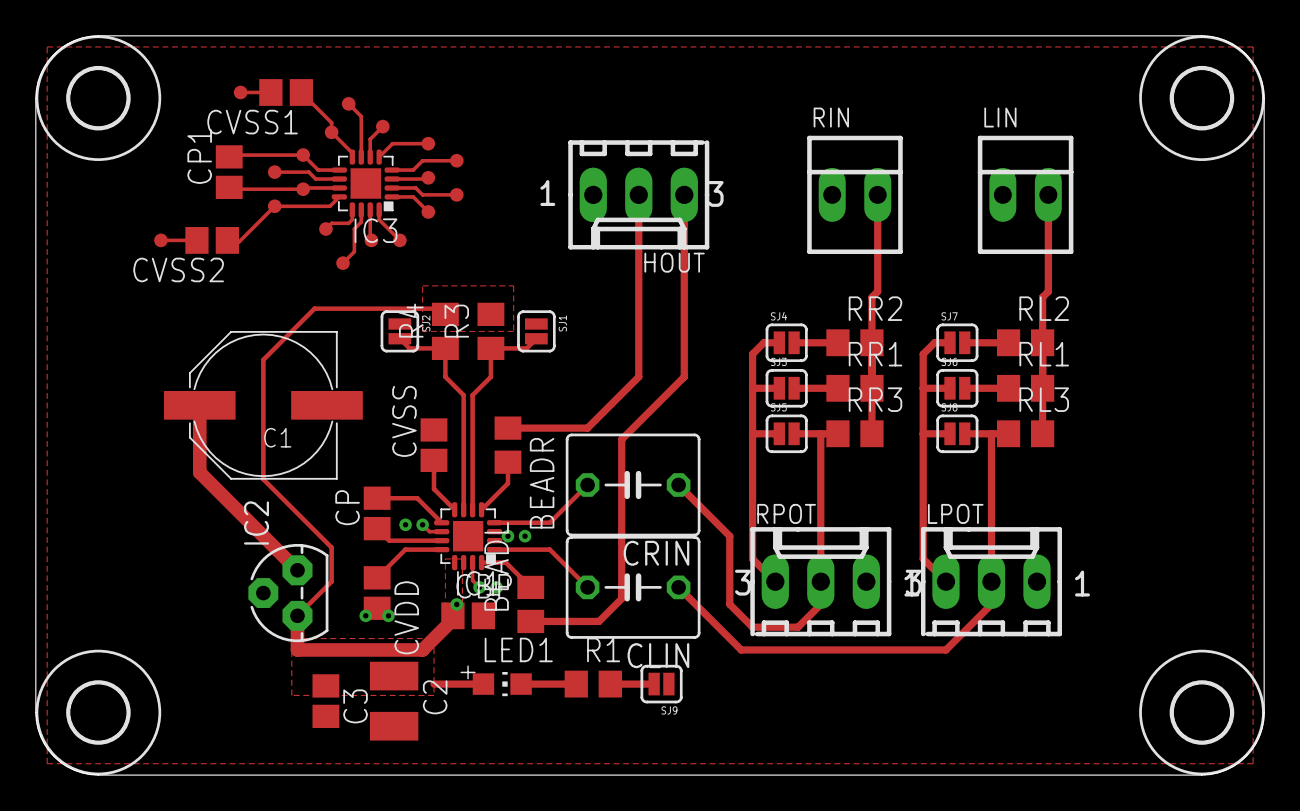
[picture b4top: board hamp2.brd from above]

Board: 2 copper layers, 68.6 x 41.3 mm, 63 parts (0 on the bottom side), 45 nets.

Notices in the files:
parts and their libraries:
SparkFun-Passives: Licensing: CC v3.0 Share-Alike You are welcome to use this library for commercial purposes.
